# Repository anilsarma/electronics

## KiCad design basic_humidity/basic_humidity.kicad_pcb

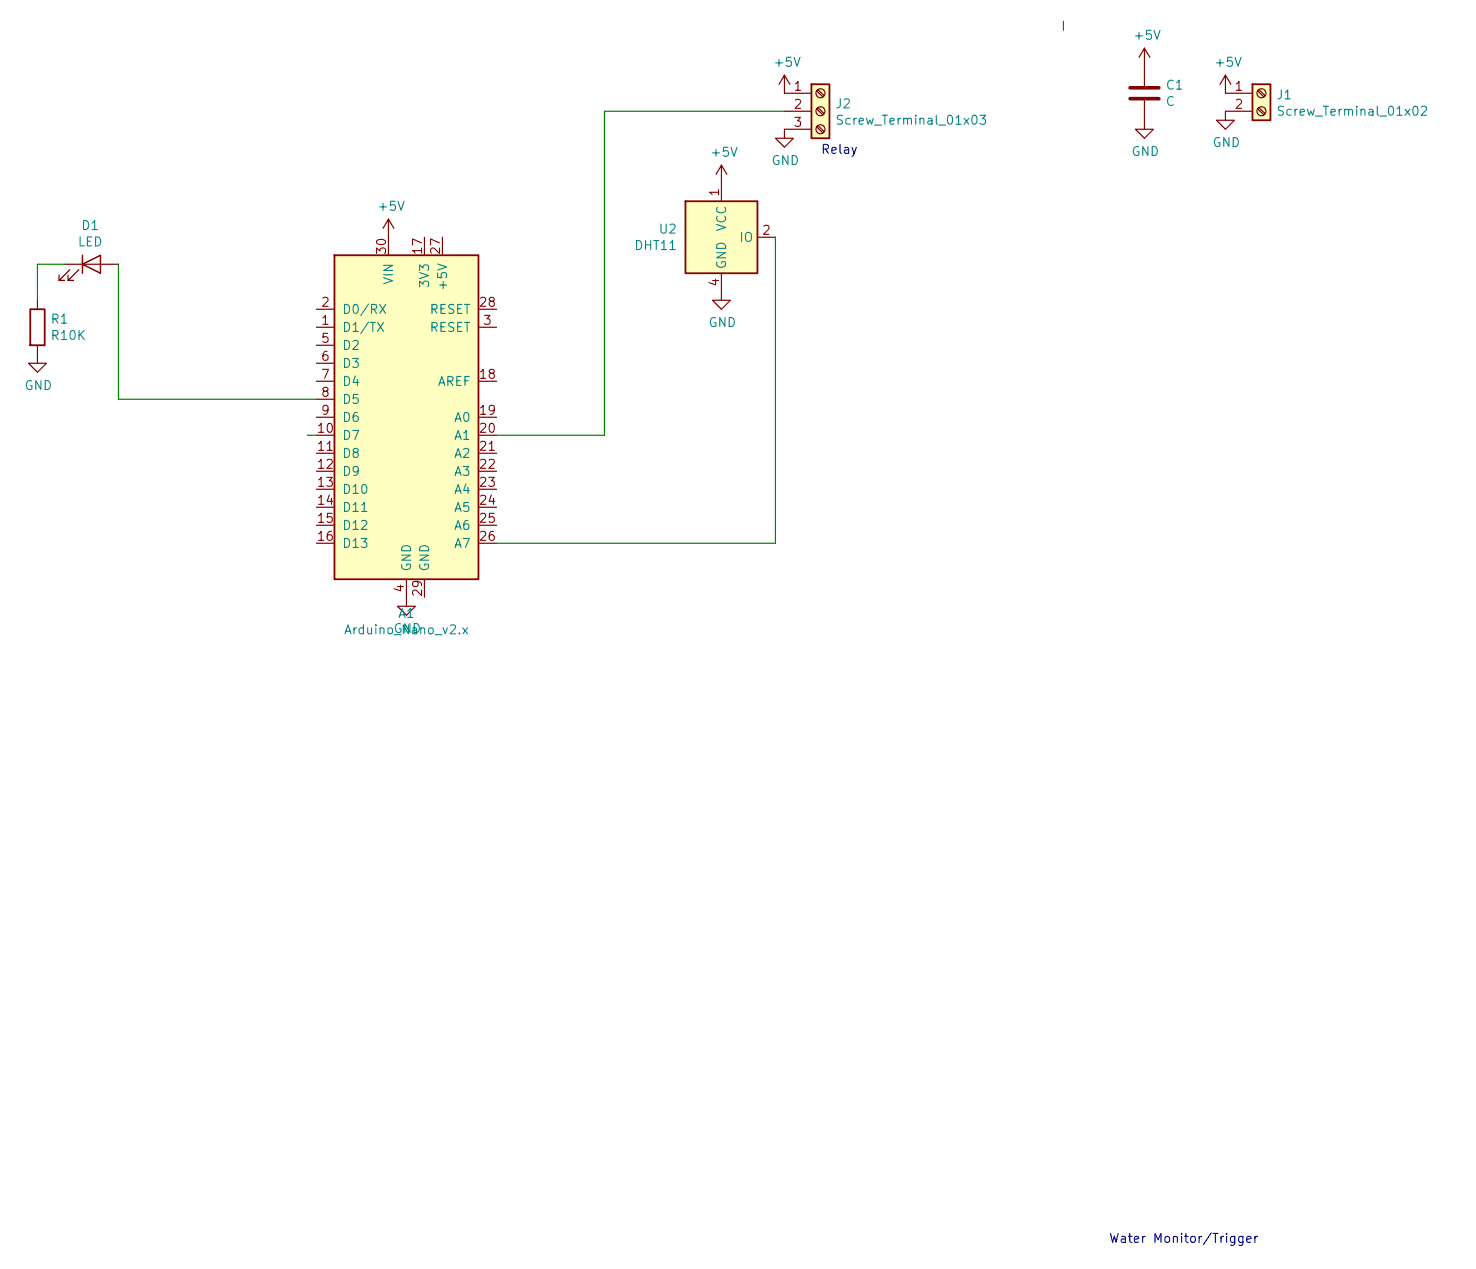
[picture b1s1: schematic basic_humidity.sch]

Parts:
A1: Arduino_Nano_v2.x; Arduino_Nano_WithMountingHoles
C1: C; C_Disc_D5.0mm_W2.5mm_P2.50mm
D1: LED; LED_D3.0mm_Clear
J1: Screw_Terminal_01x02; TerminalBlock_bornier-2_P5.08mm
J2: Screw_Terminal_01x03; TerminalBlock_bornier-3_P5.08mm
R1: R10K; R_Axial_DIN0207_L6.3mm_D2.5mm_P15.24mm_Horizontal
U2: DHT11; Aosong_DHT11_5.5x12.0_P2.54mm

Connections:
+5V: A1.30 (VIN), C1.1, J1.1, J2.1, U2.1 (VCC)
GND: A1.4 (GND), C1.2, J1.2, J2.3, R1.2, U2.4 (GND)
unnamed: A1.8 (D5), D1.2 (A)
unnamed: A1.20 (A1), J2.2
unnamed: A1.26 (A7), U2.2 (IO)
unnamed: D1.1 (K), R1.1

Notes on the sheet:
Water Monitor/Trigger
Relay

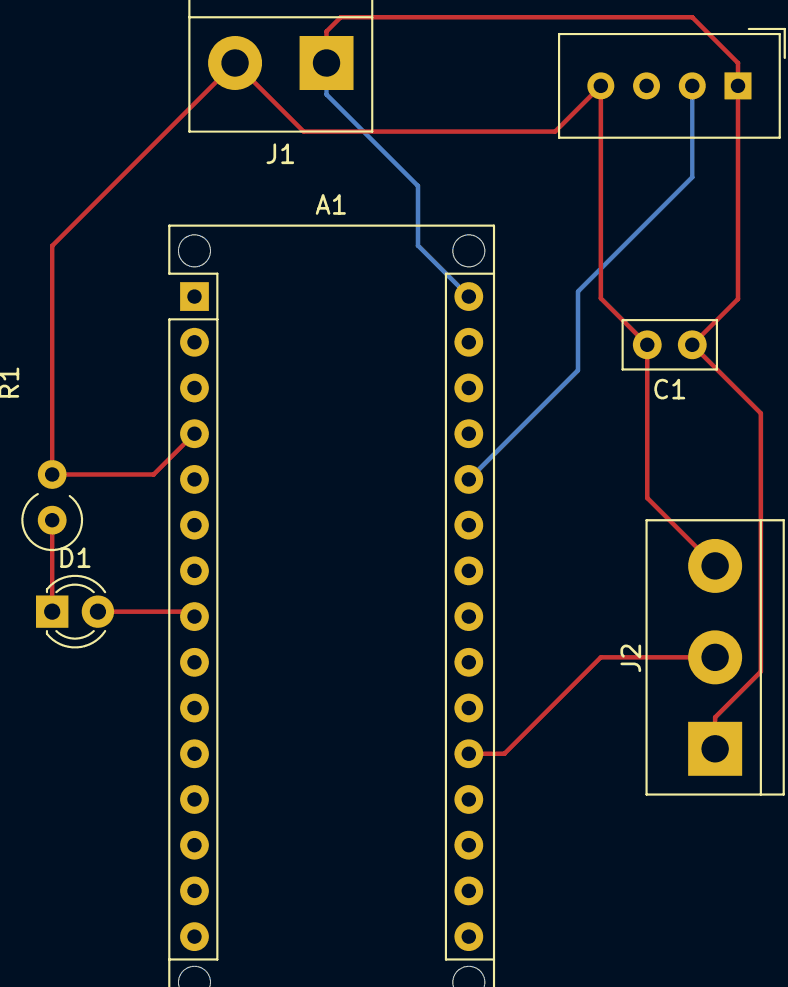
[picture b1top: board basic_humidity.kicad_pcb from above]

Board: 2 copper layers, 7 parts (0 on the bottom side), 6 nets.

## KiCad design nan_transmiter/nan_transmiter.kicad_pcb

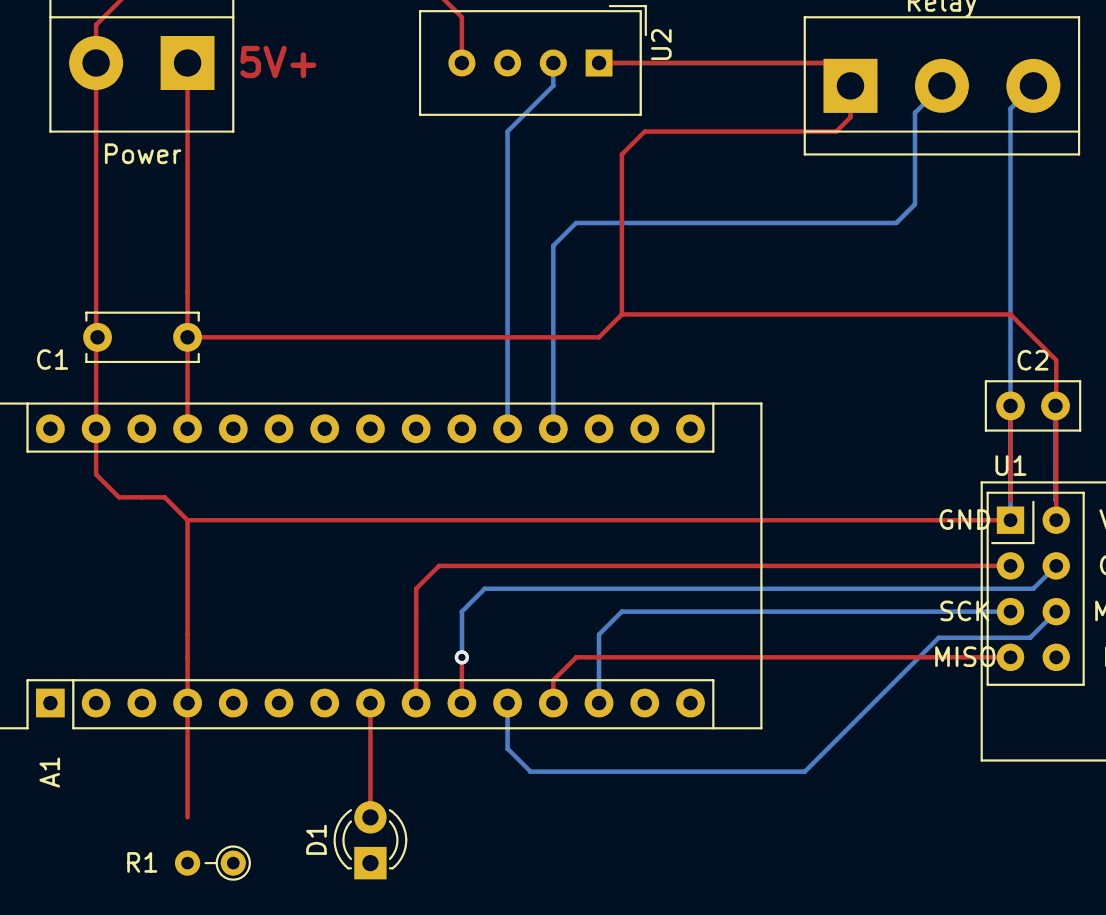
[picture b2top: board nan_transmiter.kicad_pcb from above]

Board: 2 copper layers, 9 parts (0 on the bottom side), 11 nets.

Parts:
A1: Arduino_Nano_v2.x; Arduino_Nano
C1: C; C_Disc_D6.0mm_W2.5mm_P5.00mm
C2: 10uf; C_Disc_D5.0mm_W2.5mm_P2.50mm
D1: LED; LED_D3.0mm_Clear
Power: Screw_Terminal_01x02; TerminalBlock_bornier-2_P5.08mm
R1: R; R_Axial_DIN0204_L3.6mm_D1.6mm_P2.54mm_Vertical
Relay: Screw_Terminal_01x03; TerminalBlock_bornier-3_P5.08mm
U1: NRF24L01_Breakout; nRF24L01_Breakout
U2: DHT11; Aosong_DHT11_5.5x12.0_P2.54mm

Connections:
+5V: A1.27, C1.1, Power.1, Relay.1, U1.2, U2.1
GND: A1.4, A1.29, C1.2, Power.2, R1.2, Relay.3, U1.1, U2.4
unnamed: A1.8, D1.2
unnamed: A1.9, U1.3
unnamed: A1.10, U1.4
unnamed: A1.11, U1.6
unnamed: A1.12, U1.7
unnamed: A1.13, U1.5
unnamed: A1.19, Relay.2
unnamed: A1.20, U2.2
unnamed: D1.1, R1.1

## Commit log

2019-07-14 initial
2019-08-18 update git with new menu files
2019-08-19 added lcd menu
2019-08-20 updated menu
2019-08-20 added new double click
2019-08-20 changed edit button, added montor to support pause of elements
2019-08-21 added menu
2019-08-21 dh11
2019-08-21 add nav menu
2019-08-21 add nav menu, refinement
2019-12-08 add mppt
2019-12-20 initia
2019-12-20 minor edit
